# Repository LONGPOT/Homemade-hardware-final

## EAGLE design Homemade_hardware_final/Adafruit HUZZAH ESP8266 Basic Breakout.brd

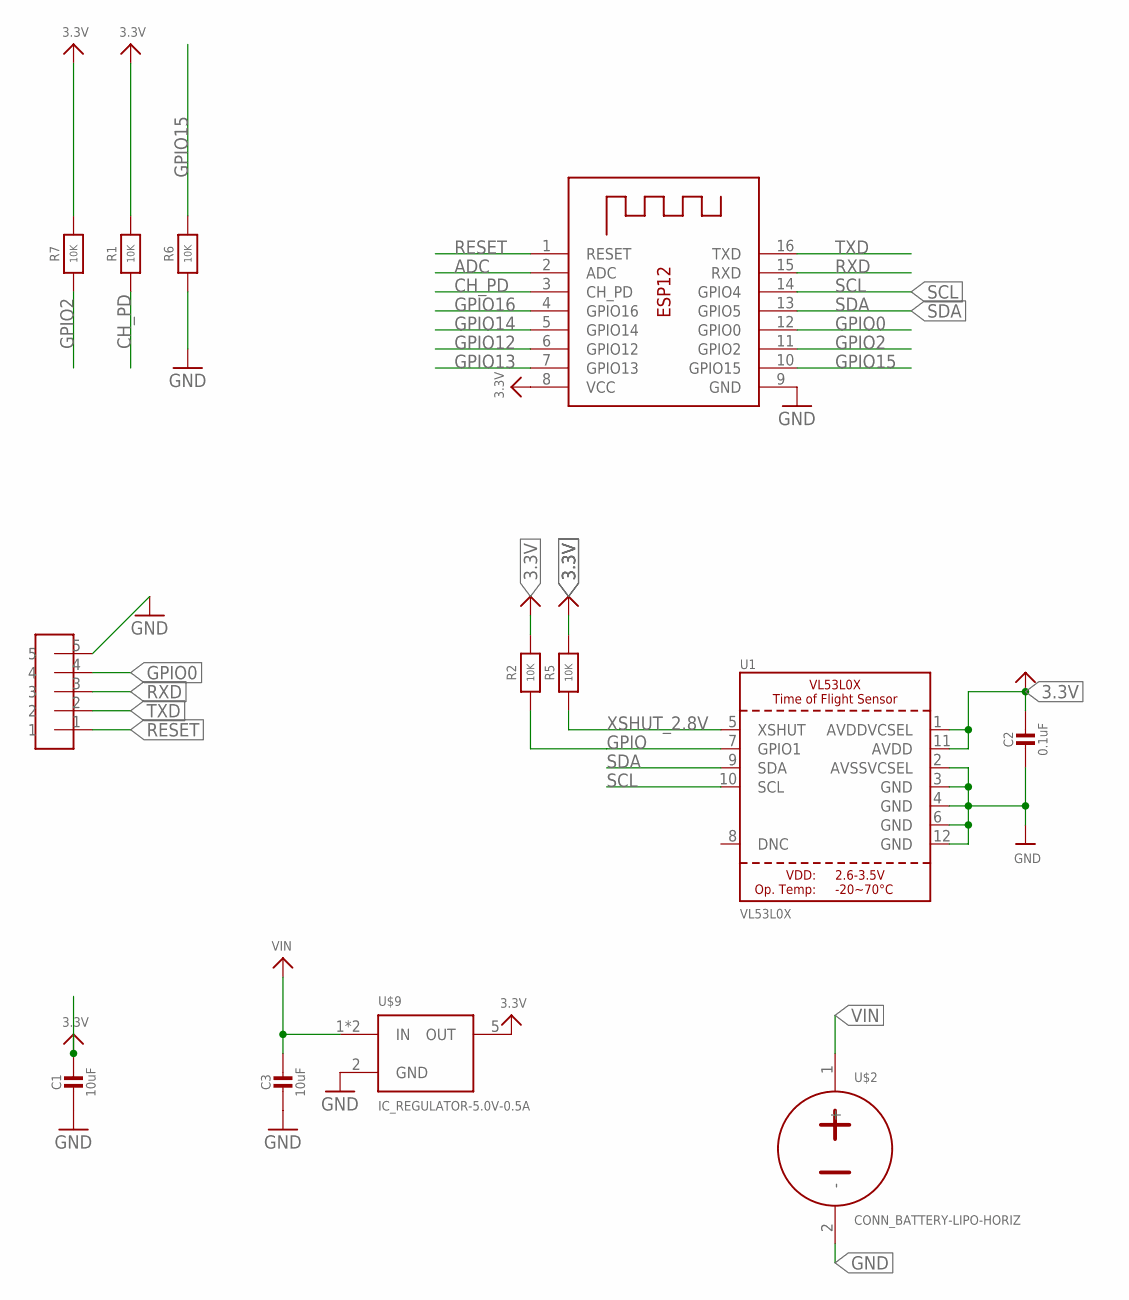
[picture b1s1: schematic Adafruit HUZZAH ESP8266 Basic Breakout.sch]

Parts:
C1, C3: 10uF; 0805-NO
C2: 0.1uF; 0805-NO
R1, R2, R5, R6, R7: 10K; 0805-NO
U1: VL53L0X; LGA12_ST
U$2: CONN_BATTERY-LIPO-HORIZ; JST-PH-2-SMT-RA
U$4: HEADER-5-TESTPOINT; TESTPOINT-5
U$9: IC_REGULATOR-5.0V-0.5A; SOT23-5
X1: ESP-12

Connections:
3.3V: C2.1, R1.2, R2.2, R5.2, R7.2, U1.1 (AVDDVCSEL), U1.11 (AVDD), U$9.5 (OUT), X1.8 (VCC)
ADC: X1.2 (ADC)
CH_PD: R1.1, X1.3 (CH_PD)
GND: C1.2, C2.2, C3.2, R6.1, U1.2 (AVSSVCSEL), U1.3 (GND), U1.4 (GND), U1.6 (GND), U1.12 (GND), U$2.2 (-), U$4.5, U$9.2 (GND), X1.9 (GND)
GPIO: R2.1, U1.7 (GPIO1)
GPIO0: U$4.4, X1.12 (GPIO0)
GPIO2: R7.1, X1.11 (GPIO2)
GPIO12: X1.6 (GPIO12)
GPIO13: X1.7 (GPIO13)
GPIO14: X1.5 (GPIO14)
GPIO15: R6.2, X1.10 (GPIO15)
GPIO16: X1.4 (GPIO16)
RESET: U$4.1, X1.1 (RESET)
RXD: U$4.3, X1.15 (RXD)
SCL: U1.10 (SCL), X1.14 (GPIO4)
SDA: U1.9 (SDA), X1.13 (GPIO5)
TXD: U$4.2, X1.16 (TXD)
VIN: C1.1, C3.1, U$2.1 (+), U$9.1 (IN), U$9.3 (IN)
XSHUT_2.8V: R5.1, U1.5 (XSHUT)

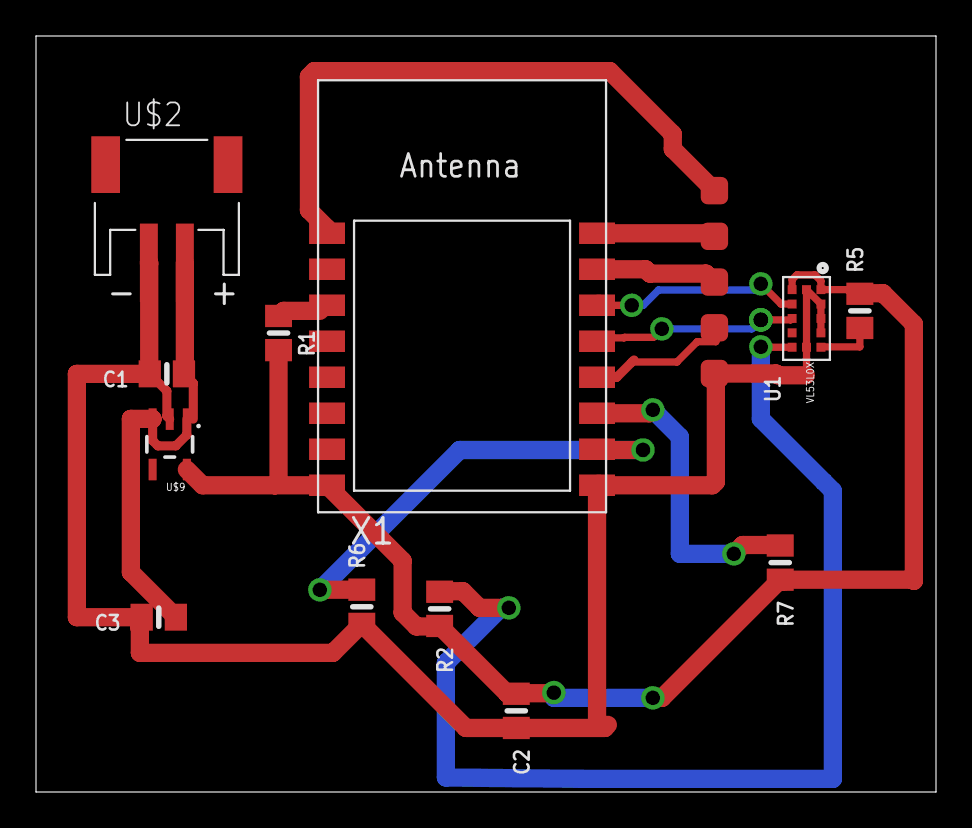
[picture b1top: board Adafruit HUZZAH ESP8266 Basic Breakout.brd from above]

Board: 2 copper layers, 50.0 x 42.0 mm, 13 parts (0 on the bottom side), 14 nets.

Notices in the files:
parts and their libraries:
microbuilder: This work is placed in the public domain, and may be freely used for commercial and non-commercial work with the following conditions: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
